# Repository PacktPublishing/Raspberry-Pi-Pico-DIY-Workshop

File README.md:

<p align='center'></p>

# Raspberry Pi Pico DIY Workshop

This is the code repository for [Raspberry Pi Pico DIY Workshop](https://www.packtpub.com/product/raspberry-pi-pico-diy-workshop/9781801814812?utm_source=github&utm_medium=repository&utm_campaign=9781801814812), published by Packt.

**Build exciting projects in home automation, personal health, gardening, and citizen science**

## What is this book about?
The Raspberry Pi Pico, Raspberry Pi family’s latest addition, is a tiny, fast, and low-cost microcontroller development board from the Raspberry Pi foundation that packs enough punch to power an extensive range of applications. Raspberry Pi Pico DIY Workshop will help you get started with your own Pico and leverage its features to develop innovative products. 

This book covers the following exciting features:
* Understand the RP2040's peripherals and apply them in the real world
* Find out about the programming languages that can be used to program the RP2040
* Delve into the applications of serial interfaces available on the Pico
* Discover add-on hardware available for the RP2040
* Explore different development board variants for the Raspberry Pi Pico
* Discover tips and tricks for seamless product development with the Pico

If you feel this book is for you, get your [copy](https://www.amazon.com/dp/1801814813) today!

## Instructions and Navigations
All of the code is organized into folders. For example, Chapter02.

The code will look like the following:
```
from machine import Pin
import utime
led = Pin(25, Pin.OUT)
while True:
```

**Following is what you need for this book:**
This book is for students, teachers, engineers, scientists, artists, and tech enthusiasts who want to develop embedded systems that drive cost-effective automation, IoT, robotics, medical devices, and art projects. If you consider yourself a maker and would like to learn how to use the Raspberry Pi Pico, then this book is for you. Familiarity with Python programming, MicroPython, CircuitPython, embedded hardware, and peripherals is helpful but not mandatory to get the most out of this book.

With the following software and hardware list you can run all code files present in the book (Chapter 1-12).
### Software and Hardware List
| Chapter | Software required | OS required |
| -------- | ------------------------------------ | ----------------------------------- |
| 1-12 | CircuitPython | Windows, Mac OS X, and Linux (Any) |
| 1-12 | MicroPython | Windows, Mac OS X, and Linux (Any) |
| 1-12 | Arduino IDE (C/C++) | Windows, Mac OS X, and Linux (Any) |

We also provide a PDF file that has color images of the screenshots/diagrams used in this book. [Click here to download it](https://static.packt-cdn.com/downloads/9781801814812_ColorImages.pdf).

## Code in Action

Click on the following link to see the Code in Action:
https://bit.ly/3OZJb5Z

### Related products
* Mastering ROS for Robotics Programming - Third Edition [[Packt]](https://www.packtpub.com/product/mastering-ros-for-robotics-programming-third-edition/9781801071024?utm_source=github&utm_medium=repository&utm_campaign=9781801071024) [[Amazon]](https://www.amazon.com/dp/1801071020)

* Learn Robotics Programming - Second Edition [[Packt]](https://www.packtpub.com/product/learn-robotics-programming-second-edition/9781839218804?utm_source=github&utm_medium=repository&utm_campaign=9781839218804) [[Amazon]](https://www.amazon.com/dp/1839218800)

## Get to Know the Author
**Sai Yamanoor**
is a senior IoT applications engineer at an industrial gases company in Buffalo, NY. He has over 10 years of experience as an embedded systems expert, working on both hardware and software design and implementations. He is a co-author of two books on the use of Raspberry Pi to execute DIY projects, and he has also presented a personal health dashboard at Maker Faires across the country. Sai is currently working on projects aimed at improving the Quality of Life (QoL) for people with chronic health conditions.

**Srihari Yamanoor**
is a mechanical engineer with experience spanning medical device design, CAD/CAM, mechatronics, and sustainability. In collaboration with his brother, he develops open source hardware products aimed at public education and awareness. He has multiple certifications in quality assurance, CAD, and FEA. Besides design, manufacturing, and quality, his current interests include behavioral change and working toward active improvement in the fight against diabetes, innovation paradigms and methodologies, and the impact of AI on healthcare. He is the co-author of two books on Raspberry Pi applications and writes blogs on various topics.

## Other books by the authors
* [Raspberry Pi Mechatronics Projects HOTSHOT](https://www.packtpub.com/product/raspberry-pi-mechatronics-projects-hotshot/9781849696227?utm_source=github&utm_medium=repository&utm_campaign=9781849696227)

* [Python Programming with Raspberry Pi](https://www.packtpub.com/product/python-programming-with-raspberry-pi/9781786467577?utm_source=github&utm_medium=repository&utm_campaign=9781786467577)

* [Getting Started with Python for the Internet of Things](https://www.packtpub.com/product/getting-started-with-python-for-the-internet-of-things/9781838555795?utm_source=github&utm_medium=repository&utm_campaign=9781838555795)
### Download a free PDF

 <i>If you have already purchased a print or Kindle version of this book, you can get a DRM-free PDF version at no cost.<br>Simply click on the link to claim your free PDF.</i>
<p align="center"> <a href="https://packt.link/free-ebook/9781801814812">https://packt.link/free-ebook/9781801814812 </a> </p>

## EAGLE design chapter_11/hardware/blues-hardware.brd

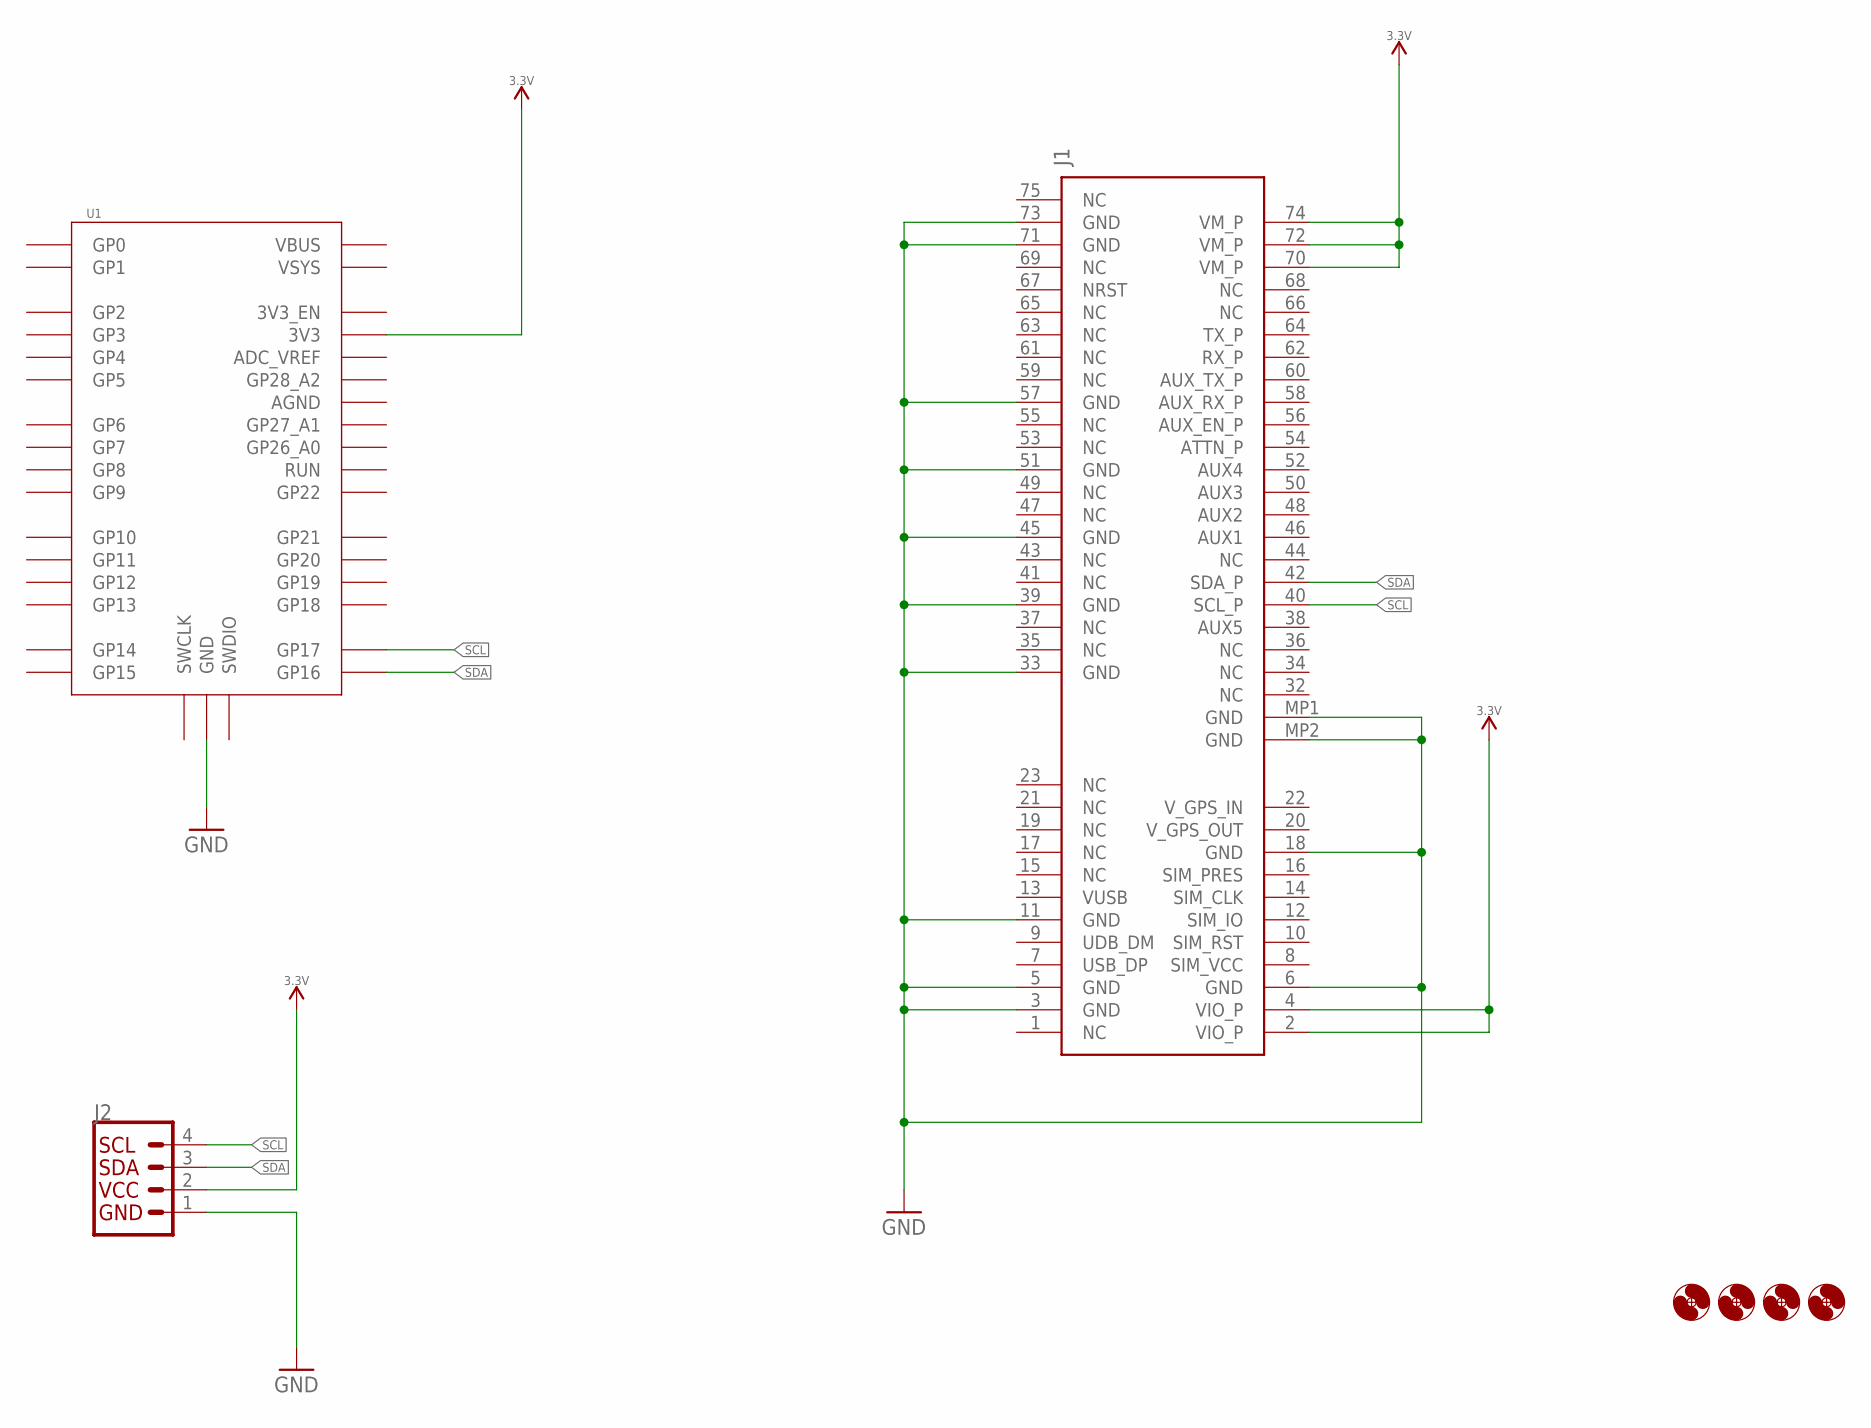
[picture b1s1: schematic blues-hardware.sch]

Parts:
H1, H2, H3, H4: MOUNT-HOLE3.0; 3,0
J1: MDT420E01001NOTECARD; NOTECARD
J2: QWIIC_CONNECTORJS-1MM; 1X04_1MM_RA
U1: RPI_PICO-TH; RPI_PICO_TH

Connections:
3.3V: J1.2 (VIO_P), J1.4 (VIO_P), J1.70 (VM_P), J1.72 (VM_P), J1.74 (VM_P), J2.2, U1.3V3
GND: J1.3 (GND), J1.5 (GND), J1.6 (GND), J1.11 (GND), J1.18 (GND), J1.33 (GND), J1.39 (GND), J1.45 (GND), J1.51 (GND), J1.57 (GND), J1.71 (GND), J1.73 (GND), J1.MP1 (GND), J1.MP2 (GND), J2.1, U1.GND@1 (GND), U1.GND@2 (GND), U1.GND@3 (GND), U1.GND@4 (GND), U1.GND@5 (GND), U1.GND@6 (GND), U1.GND@7 (GND), U1.GND@8 (GND)
SCL: J1.40 (SCL_P), J2.4, U1.GP17
SDA: J1.42 (SDA_P), J2.3, U1.GP16

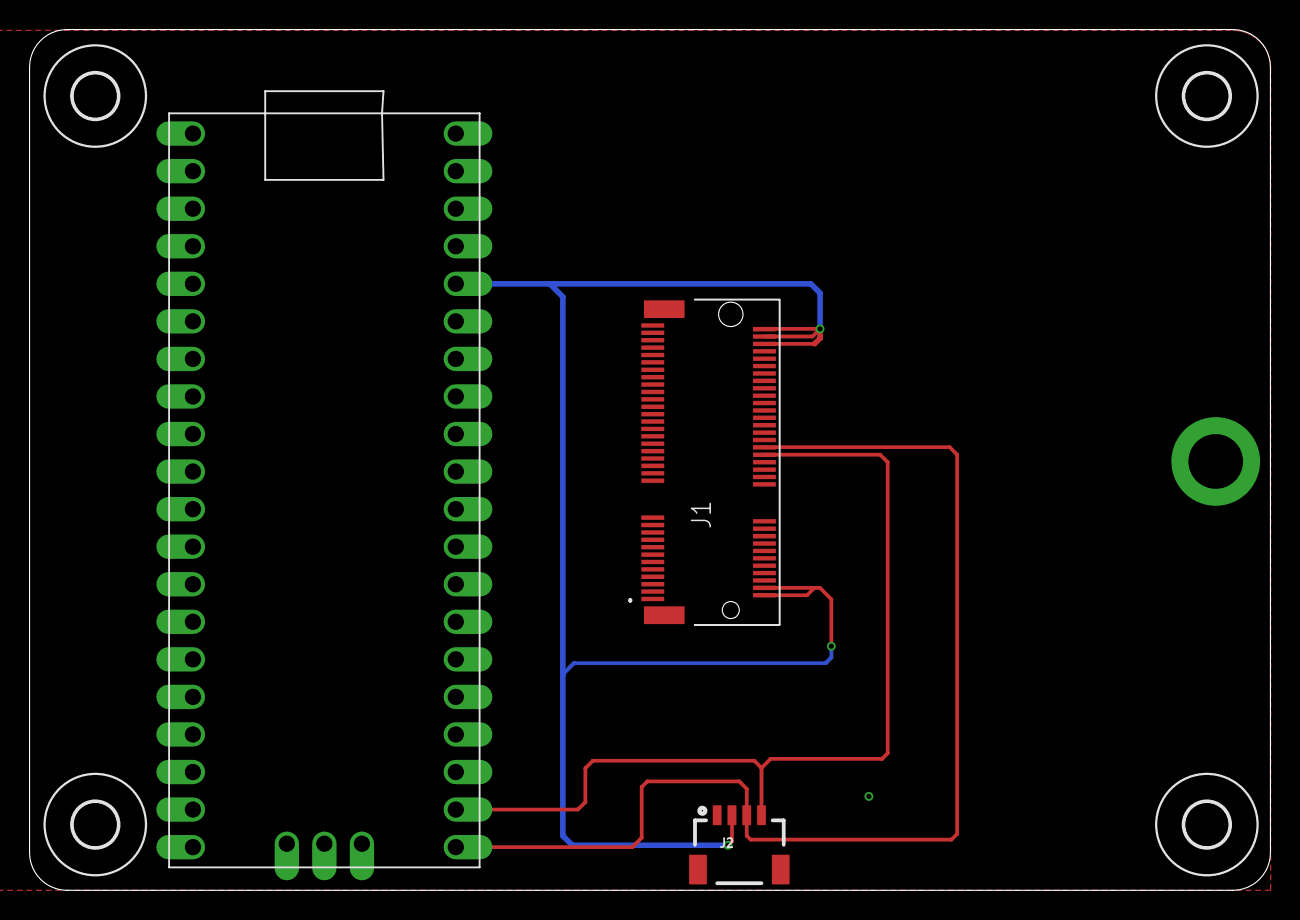
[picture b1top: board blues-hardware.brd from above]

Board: 2 copper layers, 83.9 x 58.2 mm, 7 parts (0 on the bottom side), 4 nets.

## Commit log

2021-08-23 Chapter 4
    Adding chapter 4 code samples
2021-09-03 Chapter 5 files
2021-09-07 Chapter 6
2021-10-04 chapter_6 files
2021-10-04 chapter_7
2021-10-06 chapter 7 code samples
2021-10-14 Update code_thingspeak.py
    Updates to the thingspeak example
2021-10-24 temperature sensor check-in
2021-10-25 Code file check -in
2021-11-01 chapter 2 check in
2021-11-02 temperature sensor code
2021-11-10 Checking in chapter 3
2021-11-21 Chapter 3 code samples
2021-11-24 SCD30 files
2021-11-24 Snapshots
2021-12-07 lora files
2022-02-07 Chapter 9 files
2022-03-21 Hardware files for chapter 11
    Eagle design and gerber files
2022-03-22 Gerber check-in
2022-04-04 Chapter 11 code samples
2022-04-11 servo motor check-in
2022-04-15 chapter_10 code samples
2022-04-22 BoM for Chapter 11
2022-04-22 Chapter 9 file check_in
2022-04-26 Minor changes
2022-05-01 file_rename
2022-05-02 Chapter 3 files
2022-05-02 minor_changes
2022-06-13 remove $10 campaign
2022-10-21 add free ebook notification
2023-01-24 remove 5$ campaign - 2022
2026-03-02 conference banner update

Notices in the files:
parts and their libraries:
SparkFun-Connectors: Licensing: Creative Commons ShareAlike 4.0 International - https://creativecommons.org/licenses/by-sa/4.0
